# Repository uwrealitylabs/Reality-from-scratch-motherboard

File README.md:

# Reality From Scratch Motherboard

### RP2040+ICM42688 board made by Vincent Xie (@icanc)

> [!CAUTION]
> This board has not been tested to function properly

Features:
- ICM-42688 over SPI
- TC2050 connector for debugging and GPIO testing
- LEDs for status

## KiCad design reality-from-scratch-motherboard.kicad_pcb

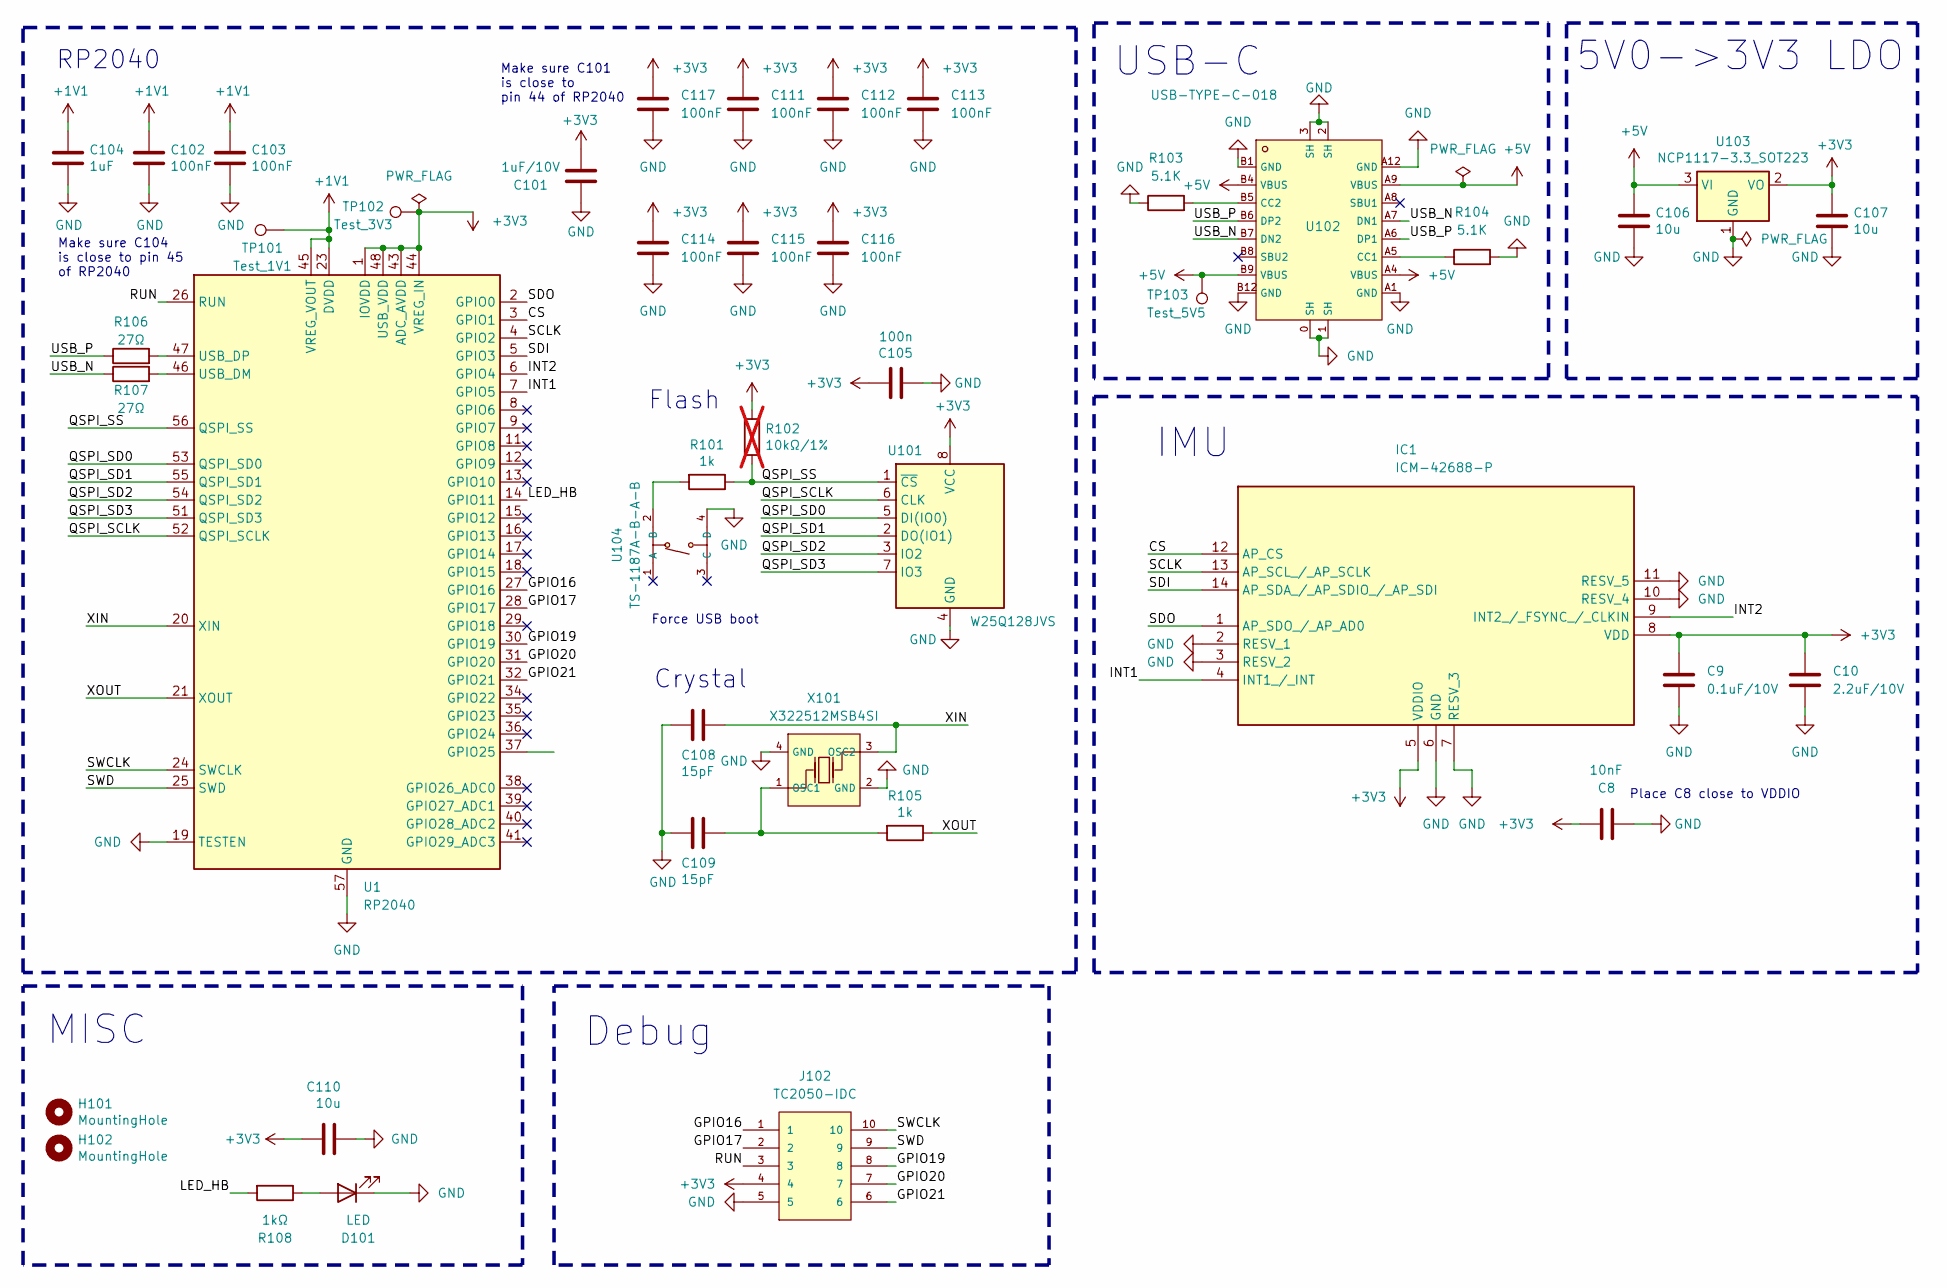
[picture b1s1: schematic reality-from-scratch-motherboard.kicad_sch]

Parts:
C8: 10nF; C_0402_1005Metric
C9: 0.1uF/10V; C_0402_1005Metric
C10: 2.2uF/10V; C_0402_1005Metric
C101: 1uF/10V; C_0402_1005Metric
C102, C103, C111, C112, C113, C114, C115, C116, C117: 100nF; C_0402_1005Metric
C104: 1uF; C_0402_1005Metric
C105: 100n; C_0402_1005Metric
C106, C107, C110: 10u; C_0402_1005Metric
C108, C109: 15pF; C_0402_1005Metric
D101: LED; LED_0603_1608Metric
H101, H102: MountingHole; MountingHole_2.7mm_M2.5
IC1: ICM-42688-P; IIM42352; Manufacturer_Part_Number ICM-42688-P; Mouser Part Number 410-ICM-42688-P
J102: TC2050-IDC; Tag-Connect_TC2050-IDC-FP_2x05_P1.27mm_Vertical; PARTREV A
R101, R105: 1k; R_0402_1005Metric
R102: 10kΩ/1%; R_0402_1005Metric; not fitted
R103, R104: 5.1K; R_0402_1005Metric
R106, R107: 27Ω; C_0402_1005Metric
R108: 1kΩ; C_0402_1005Metric
TP101: Test_1V1; TestPoint_Pad_D1.5mm
TP102: Test_3V3; TestPoint_Pad_D1.5mm
TP103: Test_5V5; TestPoint_Pad_D1.5mm
U1: RP2040; QFN-56-1EP_7x7mm_P0.4mm_EP3.2x3.2mm
U101: W25Q128JVS; SOIC-8_5.23x5.23mm_P1.27mm
U102: USB-TYPE-C-018; USB-C_SMD-TYPE-C-31-M-12; LCSC C2927038
U103: NCP1117-3.3_SOT223; SOT-223-3_TabPin2
U104: TS-1187A-B-A-B; SW-SMD_4P-L5.1-W5.1-P3.70-LS6.5-TL-2; LCSC C318884
X101: X322512MSB4SI; OSC-SMD_4P-L3.2-W2.5-BL; LCSC C9002

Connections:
+1V1: C102.1, C103.1, C104.1, TP101.1, U1.23 (DVDD), U1.45 (VREG_VOUT), U1.50 (DVDD)
+3V3: C8.1, C9.1, C10.1, C101.1, C105.1, C107.1, C110.1, C111.1, C112.1, C113.1, C114.1, C115.1, C116.1, C117.1, IC1.5 (VDDIO), IC1.8 (VDD), J102.4, R102.1, TP102.1, U1.1 (IOVDD), U1.10 (IOVDD), U1.22 (IOVDD), U1.33 (IOVDD), U1.42 (IOVDD), U1.43 (ADC_AVDD), U1.44 (VREG_IN), U1.48 (USB_VDD), U1.49 (IOVDD), U101.8 (VCC), U103.2 (VO)
+5V: C106.1, TP103.1, U102.A4 (VBUS), U102.A9 (VBUS), U102.B4 (VBUS), U102.B9 (VBUS), U103.3 (VI)
/CS: IC1.12 (AP_CS), U1.3 (GPIO1)
/GPIO16: J102.1, U1.27 (GPIO16)
/GPIO17: J102.2, U1.28 (GPIO17)
/GPIO19: J102.8, U1.30 (GPIO19)
/GPIO20: J102.7, U1.31 (GPIO20)
/GPIO21: J102.6, U1.32 (GPIO21)
/INT1: IC1.4 (INT1_/_INT), U1.7 (GPIO5)
/INT2: IC1.9 (INT2_/_FSYNC_/_CLKIN), U1.6 (GPIO4)
/LED_HB: R108.2, U1.14 (GPIO11)
/QSPI_SCLK: U1.52 (QSPI_SCLK), U101.6 (CLK)
/QSPI_SD0: U1.53 (QSPI_SD0), U101.5 (DI(IO0))
/QSPI_SD1: U1.55 (QSPI_SD1), U101.2 (DO(IO1))
/QSPI_SD2: U1.54 (QSPI_SD2), U101.3 (IO2)
/QSPI_SD3: U1.51 (QSPI_SD3), U101.7 (IO3)
/QSPI_SS: R101.1, R102.2, U1.56 (QSPI_SS), U101.1 (~CS)
/RUN: J102.3, U1.26 (RUN)
/SCLK: IC1.13 (AP_SCL_/_AP_SCLK), U1.4 (GPIO2)
/SDI: IC1.14 (AP_SDA_/_AP_SDIO_/_AP_SDI), U1.5 (GPIO3)
/SDO: IC1.1 (AP_SDO_/_AP_AD0), U1.2 (GPIO0)
/SWCLK: J102.10, U1.24 (SWCLK)
/SWD: J102.9, U1.25 (SWD)
/USB_N: R107.1, U102.A7 (DN1), U102.B7 (DN2)
/USB_P: R106.1, U102.A6 (DP1), U102.B6 (DP2)
/XIN: C108.1, U1.20 (XIN), X101.3 (OSC2)
/XOUT: R105.1, U1.21 (XOUT)
GND: C8.2, C9.2, C10.2, C101.2, C102.2, C103.2, C104.2, C105.2, C106.2, C107.2, C108.2, C109.2, C110.2, C111.2, C112.2, C113.2, C114.2, C115.2, C116.2, C117.2, D101.1 (K), IC1.2 (RESV_1), IC1.3 (RESV_2), IC1.6 (GND), IC1.7 (RESV_3), IC1.10 (RESV_4), IC1.11 (RESV_5), J102.5, R103.1, R104.2, U1.19 (TESTEN), U1.57 (GND), U101.4 (GND), U102.0 (SH), U102.1 (SH), U102.2 (SH), U102.3 (SH), U102.A1 (GND), U102.A12 (GND), U102.B1 (GND), U102.B12 (GND), U103.1 (GND), U104.4 (D), X101.2 (GND), X101.4 (GND)
unnamed: D101.2 (A), R108.1
unnamed: R107.2, U1.46 (USB_DM)
unnamed: R106.2, U1.47 (USB_DP)
unnamed: R104.1, U102.A5 (CC1)
unnamed: R103.2, U102.B5 (CC2)
unnamed: R101.2, U104.2 (B)
unnamed: C109.1, R105.2, X101.1 (OSC1)

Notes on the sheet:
Crystal
RP2040
Make sure C101 is close to pin 44 of RP2040
5V0->3V3 LDO
Make sure C104 is close to pin 45 of RP2040
MISC
USB-C
Place C8 close to VDDIO
Debug
Flash
IMU
Force USB boot

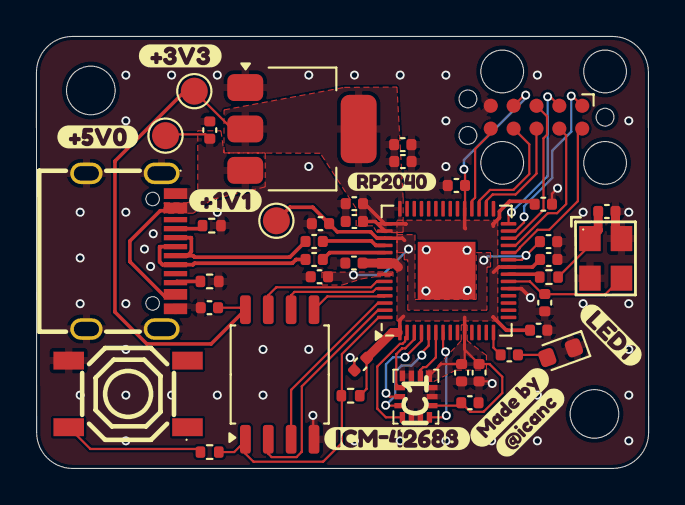
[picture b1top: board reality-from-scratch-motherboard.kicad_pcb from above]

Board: 2 copper layers, 34.0 x 24.0 mm, 50 parts (0 on the bottom side), 36 nets.

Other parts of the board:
kibuzzard-66F14AE0: G***; kibuzzard-66F14AE0
kibuzzard-66F14B1E: G***; kibuzzard-66F14B1E
kibuzzard-66F14B33: G***; kibuzzard-66F14B33
kibuzzard-66F144BA: G***; kibuzzard-66F144BA
kibuzzard-66F1440E: G***; kibuzzard-66F1440E
kibuzzard-66F14516: G***; kibuzzard-66F14516
kibuzzard-66F14520: G***; kibuzzard-66F14520
kibuzzard-66F14561: G***; kibuzzard-66F14561

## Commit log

2024-08-29 added submodule library
2024-08-29 removed extra folder
2024-08-29 basic design done
2024-09-22 schematics first revision done
2024-09-23 fixed MD file
2024-09-23 Create LICENSE
